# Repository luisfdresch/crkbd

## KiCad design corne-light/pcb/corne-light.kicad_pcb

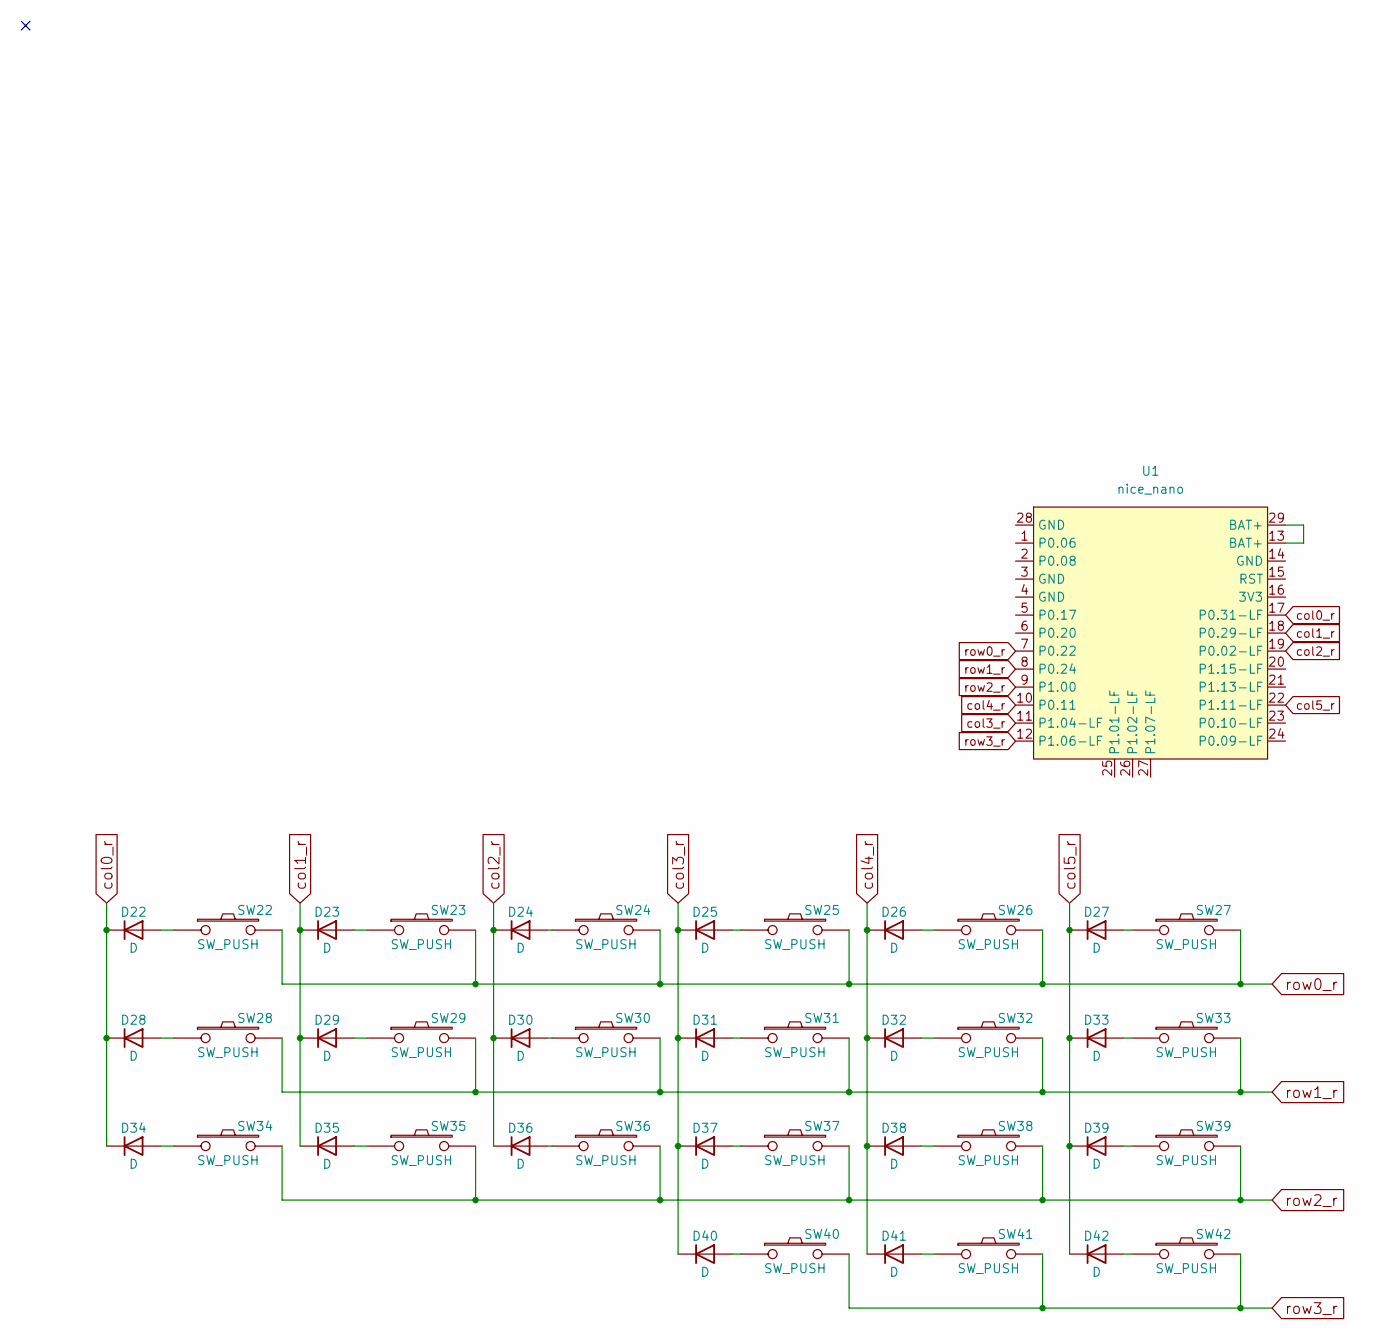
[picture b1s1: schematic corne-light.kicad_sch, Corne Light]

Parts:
D22, D23, D24, D25, D26, D28, D29, D30, D31, D32, D34, D35, D36, D37, D38, D39, D40, D41, D42: D; D_DO-35_SOD27_P10.16mm_Horizontal
D27, D33: D; D_DO-35_SOD27_P7.62mm_Horizontal
SW22, SW23, SW24, SW25, SW26, SW27, SW28, SW29, SW30, SW31, SW32, SW33, SW34, SW35, SW36, SW37, SW38, SW39, SW40, SW41: SW_PUSH; SW_Redragon_LowProfile_PCB_1.00u
SW42: SW_PUSH; SW_Redragon_LowProfile_PCB_1.50u
U1: nice_nano; nice_nano_AH_USBup

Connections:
unnamed: D22.2 (A), SW22.1
unnamed: D23.2 (A), SW23.1
unnamed: D24.2 (A), SW24.1
unnamed: D25.2 (A), SW25.1
unnamed: D26.2 (A), SW26.1
unnamed: D27.2 (A), SW27.1
unnamed: D28.2 (A), SW28.1
unnamed: D29.2 (A), SW29.1
unnamed: D30.2 (A), SW30.1
unnamed: D31.2 (A), SW31.1
unnamed: D32.2 (A), SW32.1
unnamed: D33.2 (A), SW33.1
unnamed: D34.2 (A), SW34.1
unnamed: D35.2 (A), SW35.1
unnamed: D36.2 (A), SW36.1
unnamed: D37.2 (A), SW37.1
unnamed: D38.2 (A), SW38.1
unnamed: D39.2 (A), SW39.1
unnamed: D40.2 (A), SW40.1
unnamed: D41.2 (A), SW41.1
unnamed: D42.2 (A), SW42.1
unnamed: U1.13 (BAT+), U1.29 (BAT+)
col0_r: D22.1 (K), D28.1 (K), D34.1 (K), U1.17 (P0.31-LF)
col1_r: D23.1 (K), D29.1 (K), D35.1 (K), U1.18 (P0.29-LF)
col2_r: D24.1 (K), D30.1 (K), D36.1 (K), U1.19 (P0.02-LF)
col3_r: D25.1 (K), D31.1 (K), D37.1 (K), D40.1 (K), U1.11 (P1.04-LF)
col4_r: D26.1 (K), D32.1 (K), D38.1 (K), D41.1 (K), U1.10 (P0.11)
col5_r: D27.1 (K), D33.1 (K), D39.1 (K), D42.1 (K), U1.22 (P1.11-LF)
row0_r: SW22.2, SW23.2, SW24.2, SW25.2, SW26.2, SW27.2, U1.7 (P0.22)
row1_r: SW28.2, SW29.2, SW30.2, SW31.2, SW32.2, SW33.2, U1.8 (P0.24)
row2_r: SW34.2, SW35.2, SW36.2, SW37.2, SW38.2, SW39.2, U1.9 (P1.00)
row3_r: SW40.2, SW41.2, SW42.2, U1.12 (P1.06-LF)

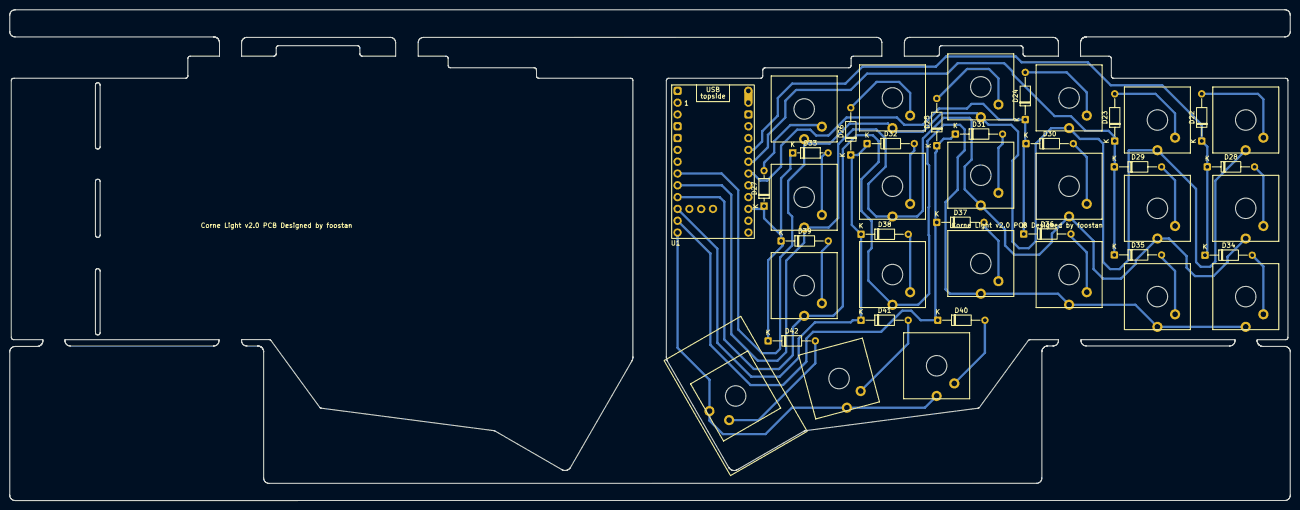
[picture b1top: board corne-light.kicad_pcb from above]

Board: 2 copper layers, 275.5 x 105.6 mm, 43 parts (0 on the bottom side), 32 nets.

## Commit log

2025-10-05 Change switches to redragon ones
2025-10-06 Change diode orientation on right side
2025-10-20 Route rightside keys
2025-11-05 Improve routing
2025-11-07 Add pcb2gcode dockerfile
2025-11-11 Improve tracks
2025-11-11 Improve clearances
